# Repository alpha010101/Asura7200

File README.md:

## ASURA7200

###
ATmega4808を使ったマイコン基板で、NXPのPCA9685という16chのPWM制御ICの評価を目的としている。用途はLEDの明るさ制御で、PWMが4096階調であることから、よくある256階調などよりも滑らかな明るさの変化が実現できる。また、PWMのクロックが高速であるためにチラつきが無い。このあたり、実際に見てみれば誰にでも分かるが、256階調や低速クロックによるチラつきのあるものとは光の質が全く違う。

同様のことを旧基板ではTIのTLC5940というICで行っていた。機能としてはPCA9685とそれほど変わらないが、TLC5940がSPIに似た制御であるのに対し、PCA9685は完全に  I2Cでの制御となっており、他のICと信号線を使い回せる点が有り難い。それ以外もPCA9685の方が応用の範囲が広いように思われる。

電源はXHコネクタから入れており、7V~35Vの入力を受け付け、それをMC7805レギュレータで5V/1Aの内部電源に落としている。これは入力に12Vや24Vを入れてLEDの駆動に使うことを前提にしているためである。このように5Vを超える電圧でLEDを駆動するために、LEDのドライバには東芝のDMOS-SINKドライバTBD62083を使用している。  
  
この他にオマケとしてRTC用としてDS1307を載せており、これもI2C制御になる。バッテリーソケットはこれのバックアップ用。

スカスカの基板に見えると思うが、旧基板にサイズやコネクタを合わせたためにこうなった。ゼロから作るならもう少しコンパクトなコネクタを使うと思う。ミスったのは、通電を示すLEDを付けなかったことで、旧基板がそうだったので忘れていた。基板上に1個のってるLEDはNeo-pixelのRGB LEDで、ソフトウェアの動作ステージなどを示す目的で設けられている。

ソフトウェア開発はArduinoを想定。ATmega4808はArduino-nano-everyなどでも使われており、それほどマイナーでは無いものの、流通しているライブラリではATmega4808を想定していない（デフォルトがATmega328)ものもかなりあり注意が必要だった。例としてはArduinoのSketchで用意された割り込みではなく、直接割り込みを操作しているようなライブラリではATmega328とATmega4808の割り込みの仕組みが違うために動作しないものがあった。  
  
設計当初は意識していなかったのだが、ATmega4808は3系統のUARTを使用可能でその後これに助けられたことがあった。

SchematicとPCB\_LayoutはAutodesk-Eagleの無償版を使用し、elecrowで製造することを想定したガーバーを作成している

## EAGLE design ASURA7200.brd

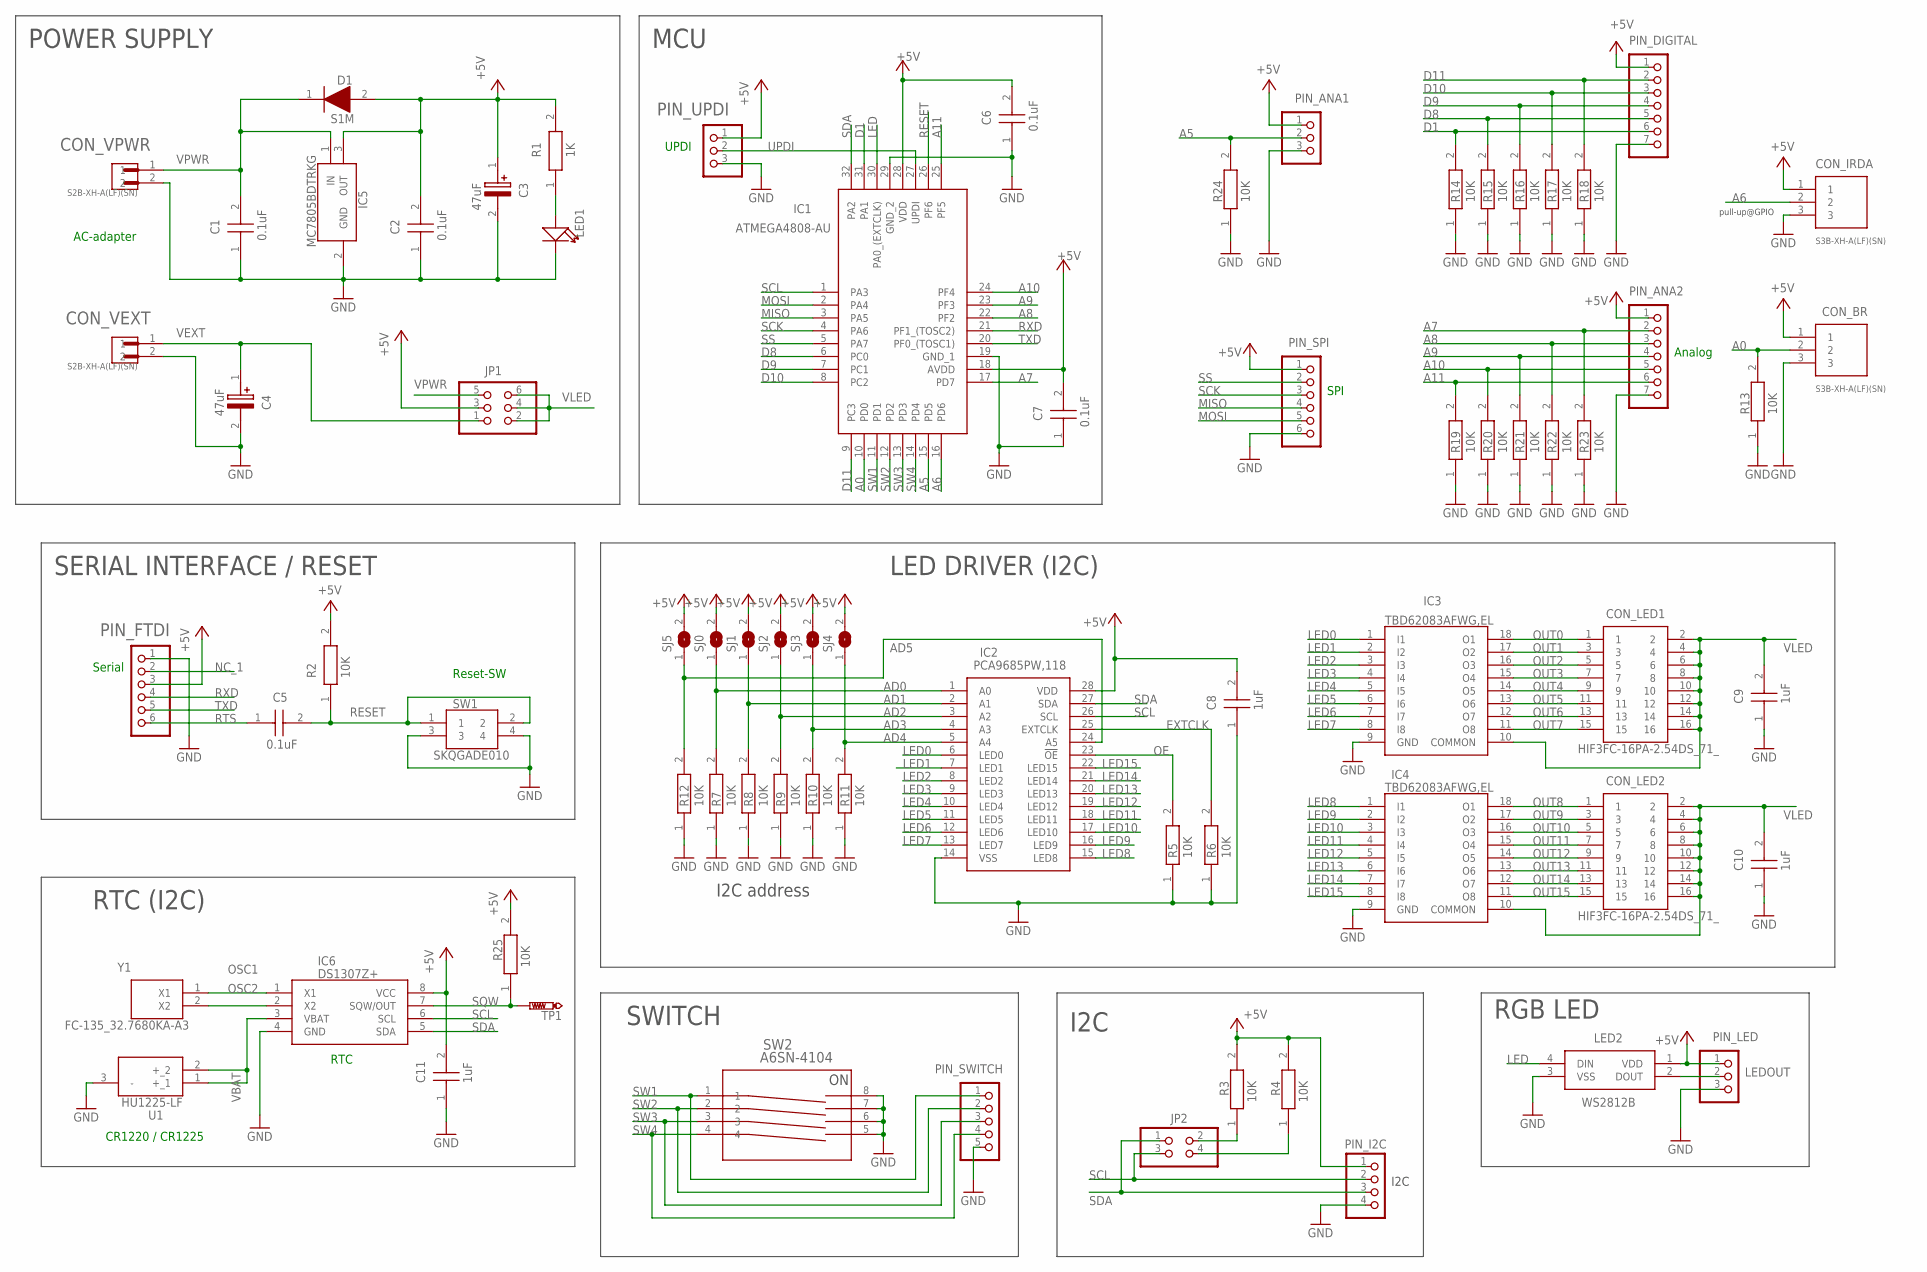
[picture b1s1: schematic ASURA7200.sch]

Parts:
C1, C8, C9, C10: CC0603KRX7R9BB104; CAPC1608X90N
C2, C5, C6, C7, C11: CC0603KRX7R8BB105; CAPC1608X90N
C3, C4: UUD1H470MCL1GS; CAPAE660X800N
CON_BR: S3B-XH-A(LF)(SN); JST_S3B-XH-A(LF)(SN)
CON_IRDA: S3B-XH-A(LF)(SN); JST_S3B-XH-A(LF)(SN)
CON_LED1, CON_LED2: HIF3FC-16PA-2.54DS_71_; SHDRRA16W69P254X254_2X8_2782X8
CON_VEXT: S2B-XH-A(LF)(SN); JST_S2B-XH-A(LF)(SN)
CON_VPWR: S2B-XH-A(LF)(SN); JST_S2B-XH-A(LF)(SN)
D1: S1M; DIOM5227X270N
IC1: ATMEGA4808-AU; QFP80P900X900X120-32N
IC2: PCA9685PW,118; SOP65P640X110-28N
IC3, IC4: TBD62083AFWG,EL; SOIC127P1032X285-18N
IC5: MC7805BDTRKG; LM317MADTRKG
IC6: DS1307Z+; SOIC127P600X175-8N
JP1: PINHD-2X3; 2X03
JP2: PINHD-2X2; 2X02
LED1: SMD-LED-CLEAR-GREEN(0603); LED-0603
LED2: WS2812B
PIN_ANA1: PINHD-1X3; 1X03
PIN_ANA2: PINHD-1X7; 1X07
PIN_DIGITAL: PINHD-1X7; 1X07
PIN_FTDI: PINHD-1X6/90; 1X06/90
PIN_I2C: PINHD-1X4; 1X04
PIN_LED: PINHD-1X3; 1X03
PIN_SPI: PINHD-1X6; 1X06
PIN_SWITCH: PINHD-1X5; 1X05
PIN_UPDI: PINHD-1X3; 1X03
R1: RC0603JR-071KL; RESC1608X55N
R2, R3, R4, R5, R6, R7, R8, R9, R10, R11, R12, R13, R14, R15, R16, R17, R18, R19, R20, R21, R22, R23, R24, R25: RC0603JR-0710KL; RESC1608X55N
SJ0, SJ1, SJ2, SJ3, SJ4, SJ5: SJ
SW1: SKQGADE010; SKQGAKE010
SW2: A6SN-4104; SW_A6SN-4104_OMR
TP1: PTR1PAD1-13; P1-13
U1: HU1225-LF; HU1225LF
Y1: FC-135_32.7680KA-A3; FC135327680KAA3

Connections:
+5V: C2.2, C3.1 (+), C6.2, C7.2, C8.2, C11.2, CON_BR.1, CON_IRDA.1, D1.2 (A), IC1.18 (AVDD), IC1.28 (VDD), IC2.28 (VDD), IC5.3 (OUT), IC6.8 (VCC), JP1.3, LED2.1 (VDD), PIN_ANA1.1, PIN_ANA2.1, PIN_DIGITAL.1, PIN_FTDI.3, PIN_I2C.1, PIN_LED.1, PIN_SPI.1, PIN_UPDI.1, R1.2, R2.2, R3.2, R4.2, R25.2, SJ0.2, SJ1.2, SJ2.2, SJ3.2, SJ4.2, SJ5.2
A0: CON_BR.2, IC1.10 (PD0), R13.2
A5: IC1.15 (PD5), PIN_ANA1.2, R24.2
A6: CON_IRDA.2, IC1.16 (PD6)
A7: IC1.17 (PD7), PIN_ANA2.2, R23.2
A8: IC1.22 (PF2), PIN_ANA2.3, R22.2
A9: IC1.23 (PF3), PIN_ANA2.4, R21.2
A10: IC1.24 (PF4), PIN_ANA2.5, R20.2
A11: IC1.25 (PF5), PIN_ANA2.6, R19.2
AD0: IC2.1 (A0), R7.2, SJ0.1
AD1: IC2.2 (A1), R8.2, SJ1.1
AD2: IC2.3 (A2), R9.2, SJ2.1
AD3: IC2.4 (A3), R10.2, SJ3.1
AD4: IC2.5 (A4), R11.2, SJ4.1
AD5: IC2.24 (A5), R12.2, SJ5.1
D1: IC1.31 (PA1), PIN_DIGITAL.6, R14.2
D8: IC1.6 (PC0), PIN_DIGITAL.5, R15.2
D9: IC1.7 (PC1), PIN_DIGITAL.4, R16.2
D10: IC1.8 (PC2), PIN_DIGITAL.3, R17.2
D11: IC1.9 (PC3), PIN_DIGITAL.2, R18.2
EXTCLK: IC2.25 (EXTCLK), R6.2
GND: C1.1, C2.1, C3.2 (-), C4.2 (-), C6.1, C7.1, C8.1, C9.1, C10.1, C11.1, CON_BR.3, CON_IRDA.3, CON_VEXT.2, CON_VPWR.2, IC1.19 (GND_1), IC1.29 (GND_2), IC2.14 (VSS), IC3.9 (GND), IC4.9 (GND), IC5.2 (GND), IC6.4 (GND), LED1.-, LED2.3 (VSS), PIN_ANA1.3, PIN_ANA2.7, PIN_DIGITAL.7, PIN_FTDI.1, PIN_I2C.4, PIN_LED.3, PIN_SPI.6, PIN_SWITCH.5, PIN_UPDI.3, R5.1, R6.1, R7.1, R8.1, R9.1, R10.1, R11.1, R12.1, R13.1, R14.1, R15.1, R16.1, R17.1, R18.1, R19.1, R20.1, R21.1, R22.1, R23.1, R24.1, SW1.3, SW1.4, SW2.5, SW2.6, SW2.7, SW2.8, U1.3 (-)
LED: IC1.30 (PA0_(EXTCLK)), LED2.4 (DIN)
LED0: IC2.6 (LED0), IC3.1 (I1)
LED1: IC2.7 (LED1), IC3.2 (I2)
LED2: IC2.8 (LED2), IC3.3 (I3)
LED3: IC2.9 (LED3), IC3.4 (I4)
LED4: IC2.10 (LED4), IC3.5 (I5)
LED5: IC2.11 (LED5), IC3.6 (I6)
LED6: IC2.12 (LED6), IC3.7 (I7)
LED7: IC2.13 (LED7), IC3.8 (I8)
LED8: IC2.15 (LED8), IC4.1 (I1)
LED9: IC2.16 (LED9), IC4.2 (I2)
LED10: IC2.17 (LED10), IC4.3 (I3)
LED11: IC2.18 (LED11), IC4.4 (I4)
LED12: IC2.19 (LED12), IC4.5 (I5)
LED13: IC2.20 (LED13), IC4.6 (I6)
LED14: IC2.21 (LED14), IC4.7 (I7)
LED15: IC2.22 (LED15), IC4.8 (I8)
LEDOUT: LED2.2 (DOUT), PIN_LED.2
LED_IN: LED1.+, R1.1
MISO: IC1.3 (PA5), PIN_SPI.4
MOSI: IC1.2 (PA4), PIN_SPI.5
NC_1: PIN_FTDI.2
OE: IC2.23 (!OE), R5.2
OSC1: IC6.1 (X1), Y1.1 (X1)
OSC2: IC6.2 (X2), Y1.2 (X2)
OUT0: CON_LED1.1, IC3.18 (O1)
OUT1: CON_LED1.3, IC3.17 (O2)
OUT2: CON_LED1.5, IC3.16 (O3)
OUT3: CON_LED1.7, IC3.15 (O4)
OUT4: CON_LED1.9, IC3.14 (O5)
OUT5: CON_LED1.11, IC3.13 (O6)
OUT6: CON_LED1.13, IC3.12 (O7)
OUT7: CON_LED1.15, IC3.11 (O8)
OUT8: CON_LED2.1, IC4.18 (O1)
OUT9: CON_LED2.3, IC4.17 (O2)
OUT10: CON_LED2.5, IC4.16 (O3)
OUT11: CON_LED2.7, IC4.15 (O4)
OUT12: CON_LED2.9, IC4.14 (O5)
OUT13: CON_LED2.11, IC4.13 (O6)
OUT14: CON_LED2.13, IC4.12 (O7)
OUT15: CON_LED2.15, IC4.11 (O8)
RESET: C5.2, IC1.26 (PF6), R2.1, SW1.1, SW1.2
RTS: C5.1, PIN_FTDI.6
RXD: IC1.21 (PF1_(TOSC2)), PIN_FTDI.4
SCK: IC1.4 (PA6), PIN_SPI.3
SCL: IC1.1 (PA3), IC2.26 (SCL), IC6.6 (SCL), JP2.3, PIN_I2C.2
SCL_1: JP2.4, R4.1
SDA: IC1.32 (PA2), IC2.27 (SDA), IC6.5 (SDA), JP2.1, PIN_I2C.3
SDA_1: JP2.2, R3.1
SQW: IC6.7 (SQW/OUT), R25.1, TP1.TP
SS: IC1.5 (PA7), PIN_SPI.2
SW1: IC1.11 (PD1), PIN_SWITCH.1, SW2.1
SW2: IC1.12 (PD2), PIN_SWITCH.2, SW2.2
SW3: IC1.13 (PD3), PIN_SWITCH.3, SW2.3
SW4: IC1.14 (PD4), PIN_SWITCH.4, SW2.4
TXD: IC1.20 (PF0_(TOSC1)), PIN_FTDI.5
UPDI: IC1.27 (UPDI), PIN_UPDI.2
VBAT: IC6.3 (VBAT), U1.1 (+_1), U1.2 (+_2)
VEXT: C4.1 (+), CON_VEXT.1, JP1.1
VLED: C9.2, C10.2, CON_LED1.2, CON_LED1.4, CON_LED1.6, CON_LED1.8, CON_LED1.10, CON_LED1.12, CON_LED1.14, CON_LED1.16, CON_LED2.2, CON_LED2.4, CON_LED2.6, CON_LED2.8, CON_LED2.10, CON_LED2.12, CON_LED2.14, CON_LED2.16, IC3.10 (COMMON), IC4.10 (COMMON), JP1.2, JP1.4, JP1.6
VPWR: C1.2, CON_VPWR.1, D1.1 (K), IC5.1 (IN), JP1.5

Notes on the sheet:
CR1220 / CR1225
Reset-SW
RTC
UPDI
Serial
AC-adapter
SPI
Analog
RTC (I2C)
SERIAL INTERFACE / RESET
POWER SUPPLY
MCU
SWITCH
pull-up@GPIO
I2C
LED DRIVER (I2C)
I2C address
RGB LED

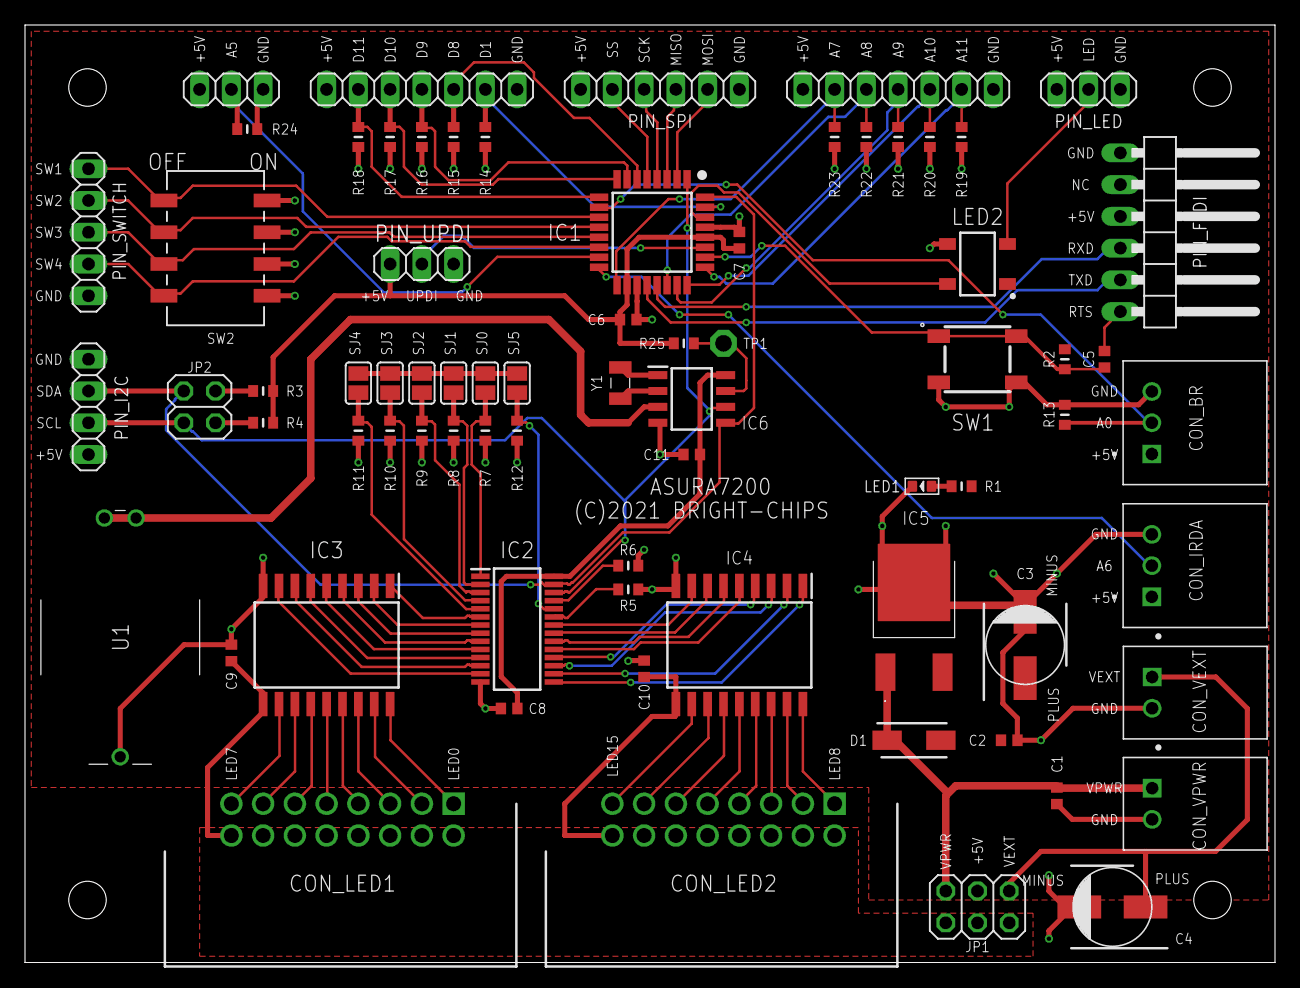
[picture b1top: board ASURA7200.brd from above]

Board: 2 copper layers, 100.0 x 75.0 mm, 73 parts (0 on the bottom side), 82 nets.

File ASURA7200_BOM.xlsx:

| Part_name_on_PCB | Device | Qty | Package | Description | MANUFACTURER_NAME | MANUFACTURER_PART_NUMBER | Source | MOUSER_PART_NUMBER | MOUSER_PRICE-STOCK
 | C1,C8,C9,C10 | CC0603KRX7R9BB104 | 4 | CAPC1608X90N | CAP, 0603 100nF +/-10% 50V | YAGEO (PHYCOMP) | CC0603KRX7R9BB104 | Elecrow
 | C2,C5,C6,C7,C11 | CC0603KRX7R8BB105 | 5 | CAPC1608X90N | CAP, 1uF 25V, 0603 | YAGEO (PHYCOMP) | CC0603KRX7R8BB105 | Elecrow
 | C3 | DV470M050E077ETR | 1 | CAPAE660X800N | CAP, 47uF, SMD 50V | CapXon | DV470M050E077ETR | Elecrow/Shenzhen
 | C4 | DV470M050E077ETR | 0 | CAPAE660X800N | No need to assemble | CapXon | DV470M050E077ETR | Elecrow/Shenzhen
 | D1 | S1M | 1 | DIOM5227X270N | RECTIFIER DIODE, STANDARD, 1A, 1000V, SMD | ON Semiconductor | S1M | Elecrow/Shenzhen
 | IC1 | ATMEGA4808-AU | 1 | QFP80P900X900X120-32N | 8-bit Microcontrollers - MCU 20MHz, 48KB, TQFP | Microchip | ATMEGA4808-AU | mouser | 556-ATMEGA4808-AU | https://www.mouser.co.uk/ProductDetail/Microchip-Technology-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
 | IC2 | PCA9685PW,118 | 1 | SOP65P640X110-28N | LED Display Drivers | NXP | PCA9685PW,118 | mouser | 771-PCA9685PW,118 | https://www.mouser.co.uk/ProductDetail/NXP-Semiconductors/PC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
 | IC3,IC4 | TBD62083AFWG,EL | 2 | SOIC127P1032X285-18N | Gate Drivers DMOS Transistor Array 8-CH, 50V/0.5A | Toshiba | TBD62083AFWG,EL | Elecrow/Shenzhen
 | IC5 | MC7805BDTRKG | 1 | LM317MADTRKG | Linear Voltage Regulators 5V 1A Positive | ON Semiconductor | MC7805BDTRKG | Elecrow/Shenzhen
 | IC6 | DS1307Z+ | 1 | SOIC127P600X175-8N | DS1307Z+, RTC,I2C, 5V, 8-Pin SOIC | Maxim Integrated | DS1307Z+ | Elecrow/Shenzhen
 | LED1 | SMD-LED-CLEAR-GREEN(0603) | 1 | LED-0603 | SMD LED, SKU=304090057 | Everlight | 17-215SYGC/S530-E2/TR8 | Elecrow |  | https://media.digikey.com/pdf/Data%20Sheets/Everlight%20PDFs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
 | LED2 | WS2812B | 1 | WS2812B | Intelligent control LED SMD5050, SKU=304990003 | Worldsemi | WS2812B | Elecrow |  | https://statics3.seeedstudio.com/images/opl/datasheet/304990003.pdf
 | R1 | RC0603JR-071KL | 1 | RESC1608X55N | RES, THICK FILM, 1K, 5%, 0.1W, 0603 | YAGEO (PHYCOMP) | RC0603JR-071KL | Elecrow
 | R2~R13,R25 | RC0603JR-0710KL | 13 | RESC1608X55N | RES, THICK FILM, 10K, 5%, 0.1W, 0603 | YAGEO (PHYCOMP) | RC0603JR-0710KL | Elecrow
 | R14~R24 | RC0603JR-0710KL | 0 | RESC1608X55N | No need to assemble | YAGEO (PHYCOMP) | RC0603JR-0710KL | Elecrow
 | SW1 | SKQGADE010 | 1 | SKQGAKE010 | Tact switch,SMT,SPST,SPST-NO 50 mA 1.5mm | ALPS | SKQGADE010 | Elecrow
 | SW2 | A6SN-4104 | 1 | SW_A6SN-4104_OMR | DIP switch | OMRON | A6SN-4104 | mouser | 653-A6SN-4104 | https://www.mouser.jp/ProductDetail/Omron-Electronics/A6SN-4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
 | Y1 | FC-135 32.7680KA-A3 | 1 | FC-135 32.7680KA-A3 | Crystals 32.768KHz 20ppm 12.5pF -40C -85C | Epson Timing | FC-135 32.7680KA-A3 | mouser | 732-FC135-32.76KAA3 | https://www.mouser.jp/ProductDetail/Epson-Timing/FC-135-3276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
 | CON_BR,CON_IRDA | S3B-XH-A(LF)(SN) | 0 |  | No need to assemble | JST
 | CON_LED1,CON_LED2 | HIF3FC-16PA-2.54DS_71_ | 0 |  | No need to assemble | Hirose
 | CON_VEXT,CON_VPWR | S2B-XH-A(LF)(SN) | 0 |  | No need to assemble | JST
 | JP1 | PINHD-2X3 | 0 | 2X03 | No need to assemble
 | JP2 | PINHD-2X2 | 0 | 2X02 | No need to assemble
 | PIN_ANA1 ,PIN_LED,PIN_UPDI | PINHD-1X3 | 0 | 1X03 | No need to assemble
 | PIN_ANA2,PIN_DIGITAL | PINHD-1X7 | 0 | 1X07 | No need to assemble
 | PIN_FTDI | PINHD-1X6/90 | 0 | 1X06/90 | No need to assemble
 | PIN_I2C | PINHD-1X4 | 0 | 1X04 | No need to assemble
 | PIN_SPI | PINHD-1X6 | 0 | 1X06 | No need to assemble
 | PIN_SWITCH | PINHD-1X5 | 0 | 1X05 | No need to assemble
 | U1 | HU1225-LF | 0 | HU1225LF | No need to assemble | RENATA
 | SJ0~SJ5 | SJ | 6 | SJ | SMD solder JUMPER

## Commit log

2024-12-31 Initial release

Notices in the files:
ASURA7200.brd:
(C)2021 BRIGHT-CHIPS
parts and their libraries:
COPYRIGHT: Copyright (C) 2018 Accelerated Designs. All rights reserved
